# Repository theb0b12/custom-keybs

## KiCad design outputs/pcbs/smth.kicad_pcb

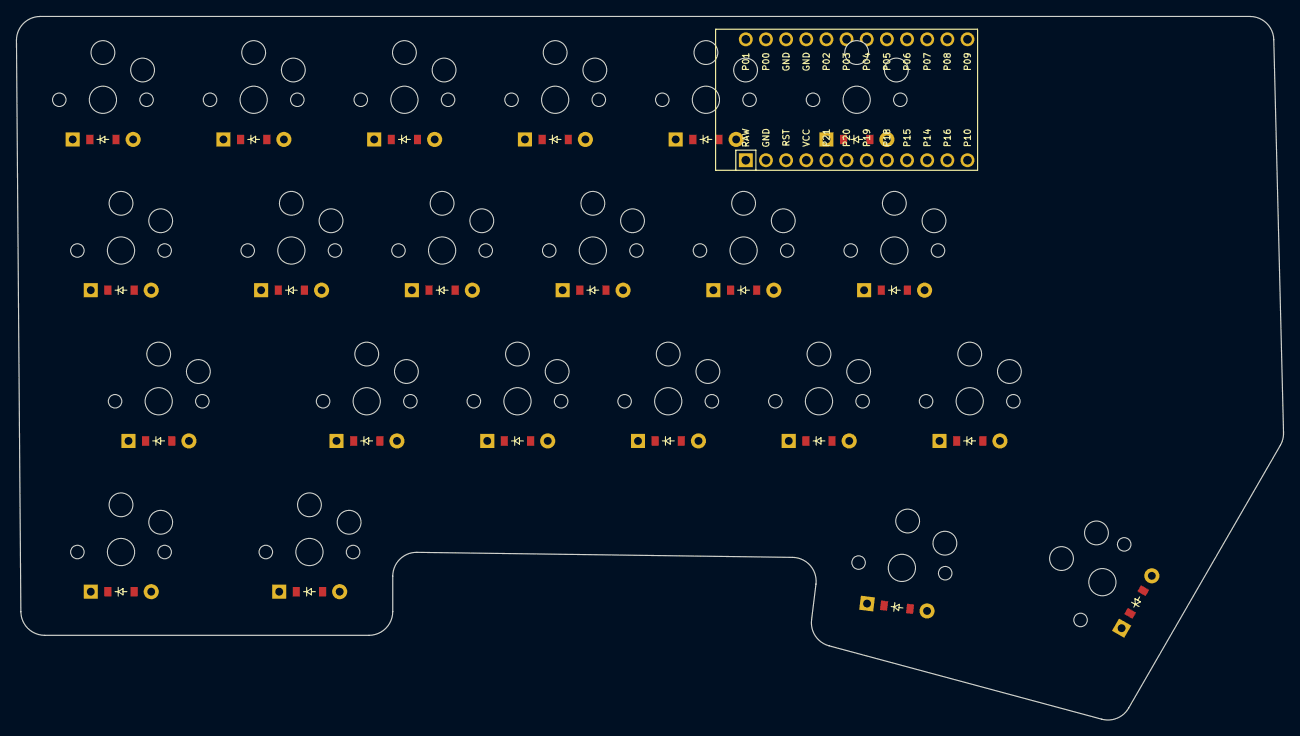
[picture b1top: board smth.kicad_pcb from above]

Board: 2 copper layers, 159.7 x 88.7 mm, 45 parts (0 on the bottom side), 23 nets, no tracks yet.

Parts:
D1, D2, D3, D4, D5, D6, D7, D8, D9, D10, D11, D12, D13, D14, D15, D16, D17, D18, D19, D20, D21, D22: ComboDiode
MCU1: ProMicro
S1, S2, S3, S4, S5, S6, S7, S8, S9, S10, S11, S12, S13, S14, S15, S16, S17, S18, S19, S20, S21, S22: PG1350

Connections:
GND: MCU1.2, MCU1.15, MCU1.16
a_default: D8.2, S8.2
b_default: D18.2, S18.2
c_default: D16.2, S16.2
d_default: D10.2, S10.2
e_default: D4.2, S4.2
esc_default: D1.2, S1.2
f_default: D11.2, S11.2
g_default: D12.2, S12.2
lctrl_default: D19.2, S19.2
lower_default: D21.2, S21.2
lshift_default: D13.2, S13.2
q_default: D2.2, S2.2
r_default: D5.2, S5.2
s_default: D9.2, S9.2
space_default: D22.2, S22.2
super_default: D20.2, S20.2
t_default: D6.2, S6.2
tab_default: D7.2, S7.2
v_default: D17.2, S17.2
w_default: D3.2, S3.2
x_default: D15.2, S15.2
z_default: D14.2, S14.2
